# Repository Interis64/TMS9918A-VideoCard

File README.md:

# TMS9918A-VideoCard

Interis 64 Video Card with TMS9918A chip

## Notes

The TMS9918A only requires 4116 DRAM, but to simplify voltage requirements, 4164 DRAM is used instead, as 4164 DRAM only requires a single 5V supply, while 4116 requires a 12V and -5V supply as well. The extra memory space is unused.

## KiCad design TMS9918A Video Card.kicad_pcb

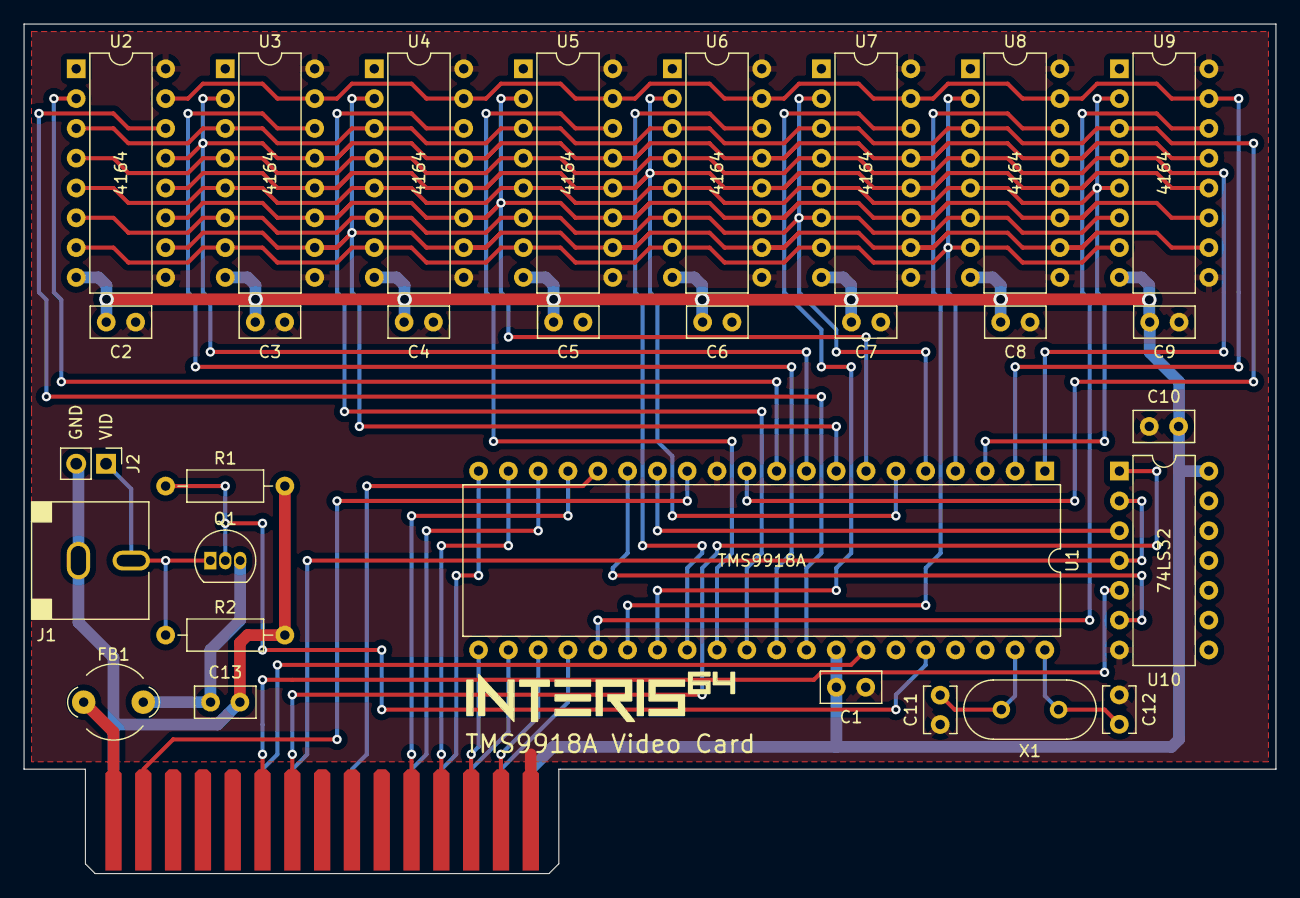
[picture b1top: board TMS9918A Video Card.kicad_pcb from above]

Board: 2 copper layers, 106.7 x 72.4 mm, 31 parts (0 on the bottom side), 44 nets.

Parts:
C1, C2, C3, C4, C5, C6, C7, C8, C9, C10, C13: 0.1µF; C_Disc_D5.0mm_W2.5mm_P2.50mm
C11, C12: 27pF; C_Disc_D3.8mm_W2.6mm_P2.50mm
FB1: FerriteBead_Small; LairdTech_28C0236-0JW-10
J1: Video Out; Jack_RCA_CUI_RCJ-04
J2: Video Out; PinHeader_1x02_P2.54mm_Vertical
J4: Edge Connector; Interis_Expansion_PCBEdge
Q1: 2N4401; TO-92_Inline
R1: 470; R_Axial_DIN0207_L6.3mm_D2.5mm_P10.16mm_Horizontal
R2: 75; R_Axial_DIN0207_L6.3mm_D2.5mm_P10.16mm_Horizontal
U1: TMS9918A; DIP-40_W15.24mm
U2, U3, U4, U5, U6, U7, U8, U9: 4164; DIP-16_W7.62mm
U10: 74LS32; DIP-14_W7.62mm
X1: 10.738635 MHz; Crystal_HC49-U_Vertical

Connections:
+5V: C1.1, C2.1, C3.1, C4.1, C5.1, C6.1, C7.1, C8.1, C9.1, C10.1, J4.b15 (+5V), U1.33 (Vcc), U2.8 (Vcc), U3.8 (Vcc), U4.8 (Vcc), U5.8 (Vcc), U6.8 (Vcc), U7.8 (Vcc), U8.8 (Vcc), U9.8 (Vcc), U10.14 (VCC)
+5VA: FB1.1, J4.a1 (+5V)
/COMVID: Q1.2 (B), R1.1, U1.36 (COMVID)
/FilteredPower: C13.1, FB1.2, Q1.3 (C)
A0: J4.a2 (A0), U1.13 (MODE)
AD0: U1.10 (AD0), U2.2 (DI)
AD1: U1.9 (AD1), U2.13 (A6), U3.2 (DI), U3.13 (A6), U4.13 (A6), U5.13 (A6), U6.13 (A6), U7.13 (A6), U8.13 (A6), U9.13 (A6)
AD2: U1.8 (AD2), U2.10 (A5), U3.10 (A5), U4.2 (DI), U4.10 (A5), U5.10 (A5), U6.10 (A5), U7.10 (A5), U8.10 (A5), U9.10 (A5)
AD3: U1.7 (AD3), U2.11 (A4), U3.11 (A4), U4.11 (A4), U5.2 (DI), U5.11 (A4), U6.11 (A4), U7.11 (A4), U8.11 (A4), U9.11 (A4)
AD4: U1.6 (AD4), U2.12 (A3), U3.12 (A3), U4.12 (A3), U5.12 (A3), U6.2 (DI), U6.12 (A3), U7.12 (A3), U8.12 (A3), U9.12 (A3)
AD5: U1.5 (AD5), U2.6 (A2), U3.6 (A2), U4.6 (A2), U5.6 (A2), U6.6 (A2), U7.2 (DI), U7.6 (A2), U8.6 (A2), U9.6 (A2)
AD6: U1.4 (AD6), U2.7 (A1), U3.7 (A1), U4.7 (A1), U5.7 (A1), U6.7 (A1), U7.7 (A1), U8.2 (DI), U8.7 (A1), U9.7 (A1)
AD7: U1.3 (AD7), U2.5 (A0), U3.5 (A0), U4.5 (A0), U5.5 (A0), U6.5 (A0), U7.5 (A0), U8.5 (A0), U9.2 (DI), U9.5 (A0)
D0: J4.a11 (D0), U1.17 (CD7)
D1: J4.b11 (D1), U1.18 (CD6)
D2: J4.a12 (D2), U1.19 (CD5)
D3: J4.b12 (D3), U1.20 (CD4)
D4: J4.a13 (D4), U1.21 (CD3)
D5: J4.b13 (D5), U1.22 (CD2)
D6: J4.a14 (D6), U1.23 (CD1)
D7: J4.b14 (D7), U1.24 (CD0)
GND: C1.2, C2.2, C3.2, C4.2, C5.2, C6.2, C7.2, C8.2, C9.2, C10.2, C11.2, C12.1, J4.a15 (GND), U1.12 (GND), U2.9 (A7), U2.16 (GND), U3.9 (A7), U3.16 (GND), U4.9 (A7), U4.16 (GND), U5.9 (A7), U5.16 (GND), U6.9 (A7), U6.16 (GND), U7.9 (A7), U7.16 (GND), U8.9 (A7), U8.16 (GND), U9.9 (A7), U9.16 (GND), U10.7 (GND)
GNDA: C13.2, J1.2 (Ext), J2.2, J4.b1 (GND), R1.2, R2.2
unnamed: C11.1, U1.39 (X1), X1.2
unnamed: C12.2, U1.40 (X2), X1.1
unnamed: J1.1 (In), J2.1, Q1.1 (E), R2.1
unnamed: U1.14 (~CSW), U10.3
unnamed: U1.15 (~CSR), U10.6
RD0: U1.32 (RD0), U2.14 (DO)
RD1: U1.31 (RD1), U3.14 (DO)
RD2: U1.30 (RD2), U4.14 (DO)
RD3: U1.29 (RD3), U5.14 (DO)
RD4: U1.28 (RD4), U6.14 (DO)
RD5: U1.27 (RD5), U7.14 (DO)
RD6: U1.26 (RD6), U8.14 (DO)
RD7: U1.25 (RD7), U9.14 (DO)
R/~W: U1.11 (R/~W), U2.3 (~WE), U3.3 (~WE), U4.3 (~WE), U5.3 (~WE), U6.3 (~WE), U7.3 (~WE), U8.3 (~WE), U9.3 (~WE)
~CAS: U1.2 (~CAS), U2.15 (~CAS), U3.15 (~CAS), U4.15 (~CAS), U5.15 (~CAS), U6.15 (~CAS), U7.15 (~CAS), U8.15 (~CAS), U9.15 (~CAS)
~IRQ: J4.b9 (~IRQ), U1.16 (~INT)
~RAS: U1.1 (~RAS), U2.4 (~RAS), U3.4 (~RAS), U4.4 (~RAS), U5.4 (~RAS), U6.4 (~RAS), U7.4 (~RAS), U8.4 (~RAS), U9.4 (~RAS)
~RD: J4.a6 (~RD), U10.5
~RESET: J4.b6 (~RESET), U1.34 (~RESET/SYNC)
~SLOT: J4.b7 (~SLOT), U10.2, U10.4
~WR: J4.a7 (~WR), U10.1

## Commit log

2023-06-06 Schematic cleanup
